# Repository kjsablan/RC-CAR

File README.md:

# RC CAR
 PCB Design for an RC CAR (Senior Project)
This is a senior design project this is currently in development and will be complete by May 2023.
The Purpose is to design a Printed Circuit Board using the Eagle software to create a circuit schematic, convert it to a board layout, generate the gerber files, and send the files out to a company to print the board. 
Then Using a microcontroller (ATMega 328P) develop firmware and create a product (RC Car)
My group has completed creating the board and now are building the RC Car.
All files (Project Report/Journal article) are still not completed and will be complete at the end of this semester (May 2023)

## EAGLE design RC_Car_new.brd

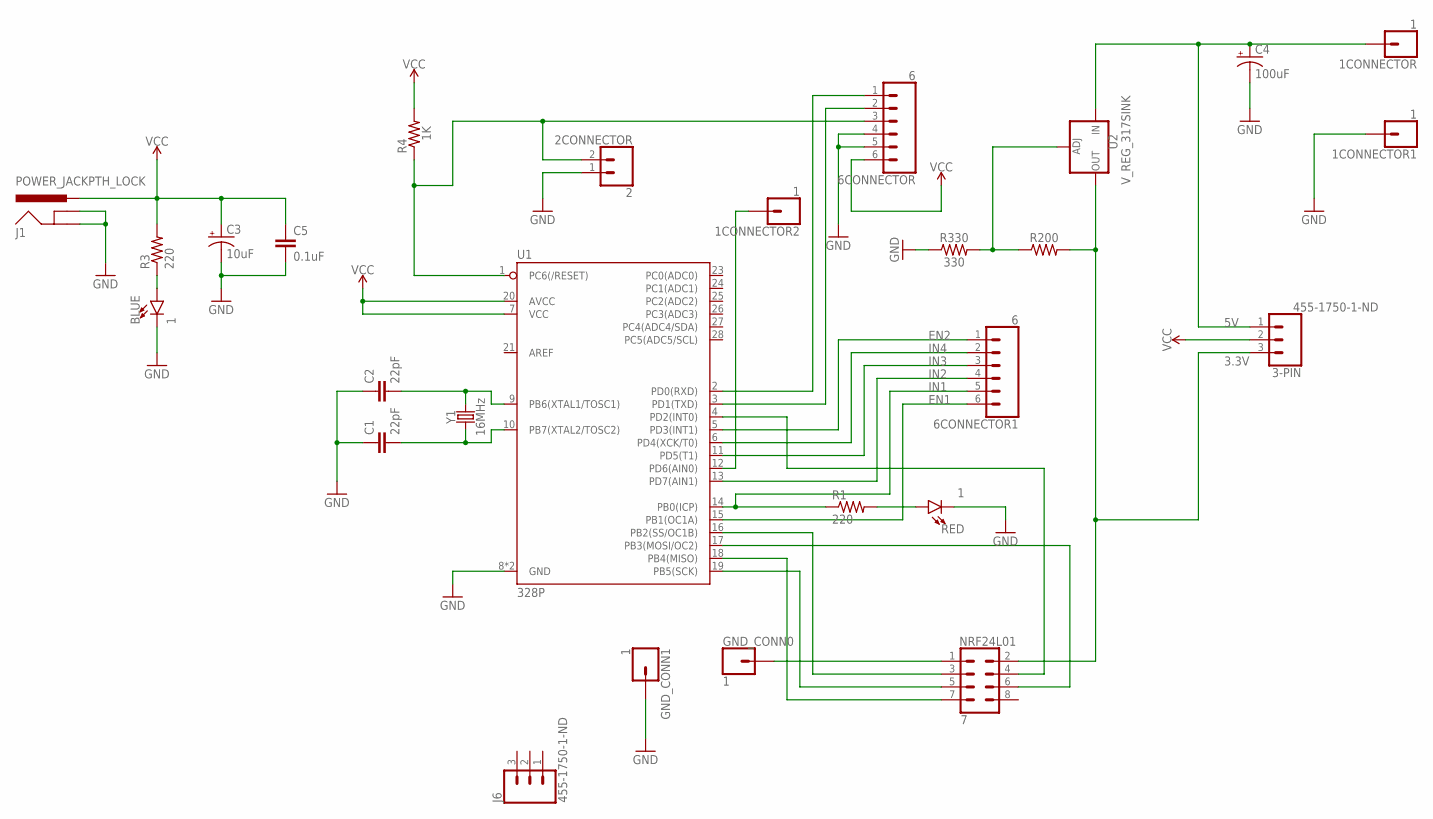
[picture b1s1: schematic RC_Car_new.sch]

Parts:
1CONNECTOR, 1CONNECTOR1, 1CONNECTOR2: 1; 1X01
2CONNECTOR: 2; 1X02
3-PIN: 455-1750-1-ND; 1X03
6CONNECTOR, 6CONNECTOR1: 6; 1X06
BLUE: 1; LED_3MM
C1, C2: 22pF; CAP-PTH-2.54
C3: 10uF; CPOL-RADIAL-2.5MM-5MM
C4: 100uF; CPOL-RADIAL-2.5MM-6.5MM
C5: 0.1uF; CAP-PTH-SMALL-KIT
GND_CONN0, GND_CONN1: 1; 1X01
J1: POWER_JACKPTH_LOCK; POWER_JACK_PTH_LOCK
J6: 455-1750-1-ND; 1X03
NRF24L01: 7; 2X4
R1, R3: 220; 0207/10
R4: 1K; 0207/10
R200: AXIAL-0.3
R330: 330; AXIAL-0.3
RED: 1; LED_3MM
U1: 328P; DIP28
U2: V_REG_317SINK; TO220-ADJ
Y1: 16MHz; HC49US

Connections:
3.3V: 3-PIN.3, NRF24L01.2, R200.P$2 (2), U2.OUT
5V: 1CONNECTOR.1, 3-PIN.1, C4.1 (+), U2.IN
EN1: 6CONNECTOR1.6, U1.15 (PB1(OC1A))
EN2: 6CONNECTOR1.1, U1.5 (PD3(INT1))
GND: 1CONNECTOR1.1, 2CONNECTOR.1, 6CONNECTOR.4, 6CONNECTOR.5, BLUE.K (C), C1.1, C2.1, C3.2 (-), C4.2 (-), C5.2, GND_CONN1.1, J1.GND, J1.GNDBREAK, R330.P$1 (1), RED.K (C), U1.8 (GND), U1.22 (GND)
IN1: 6CONNECTOR1.5, R1.1, U1.14 (PB0(ICP))
IN2: 6CONNECTOR1.4, U1.13 (PD7(AIN1))
IN3: 6CONNECTOR1.3, U1.11 (PD5(T1))
IN4: 6CONNECTOR1.2, U1.6 (PD4(XCK/T0))
unnamed: 2CONNECTOR.2, 6CONNECTOR.3, R4.1, U1.1 (PC6(/RESET))
unnamed: BLUE.A, R3.1
unnamed: C2.2, U1.9 (PB6(XTAL1/TOSC1)), Y1.2
unnamed: C1.2, U1.10 (PB7(XTAL2/TOSC2)), Y1.1
unnamed: 1CONNECTOR2.1, U1.12 (PD6(AIN0))
unnamed: R1.2, RED.A
unnamed: GND_CONN0.1, NRF24L01.1
unnamed: NRF24L01.3, U1.16 (PB2(SS/OC1B))
unnamed: 6CONNECTOR.1, U1.2 (PD0(RXD))
unnamed: 6CONNECTOR.2, U1.3 (PD1(TXD))
unnamed: R200.P$1 (1), R330.P$2 (2), U2.ADJ
unnamed: NRF24L01.4, U1.4 (PD2(INT0))
unnamed: NRF24L01.6, U1.17 (PB3(MOSI/OC2))
unnamed: NRF24L01.5, U1.19 (PB5(SCK))
unnamed: NRF24L01.7, U1.18 (PB4(MISO))
VCC: 3-PIN.2, 6CONNECTOR.6, C3.1 (+), C5.1, J1.PWR, R3.2, R4.2, U1.7 (VCC), U1.20 (AVCC)

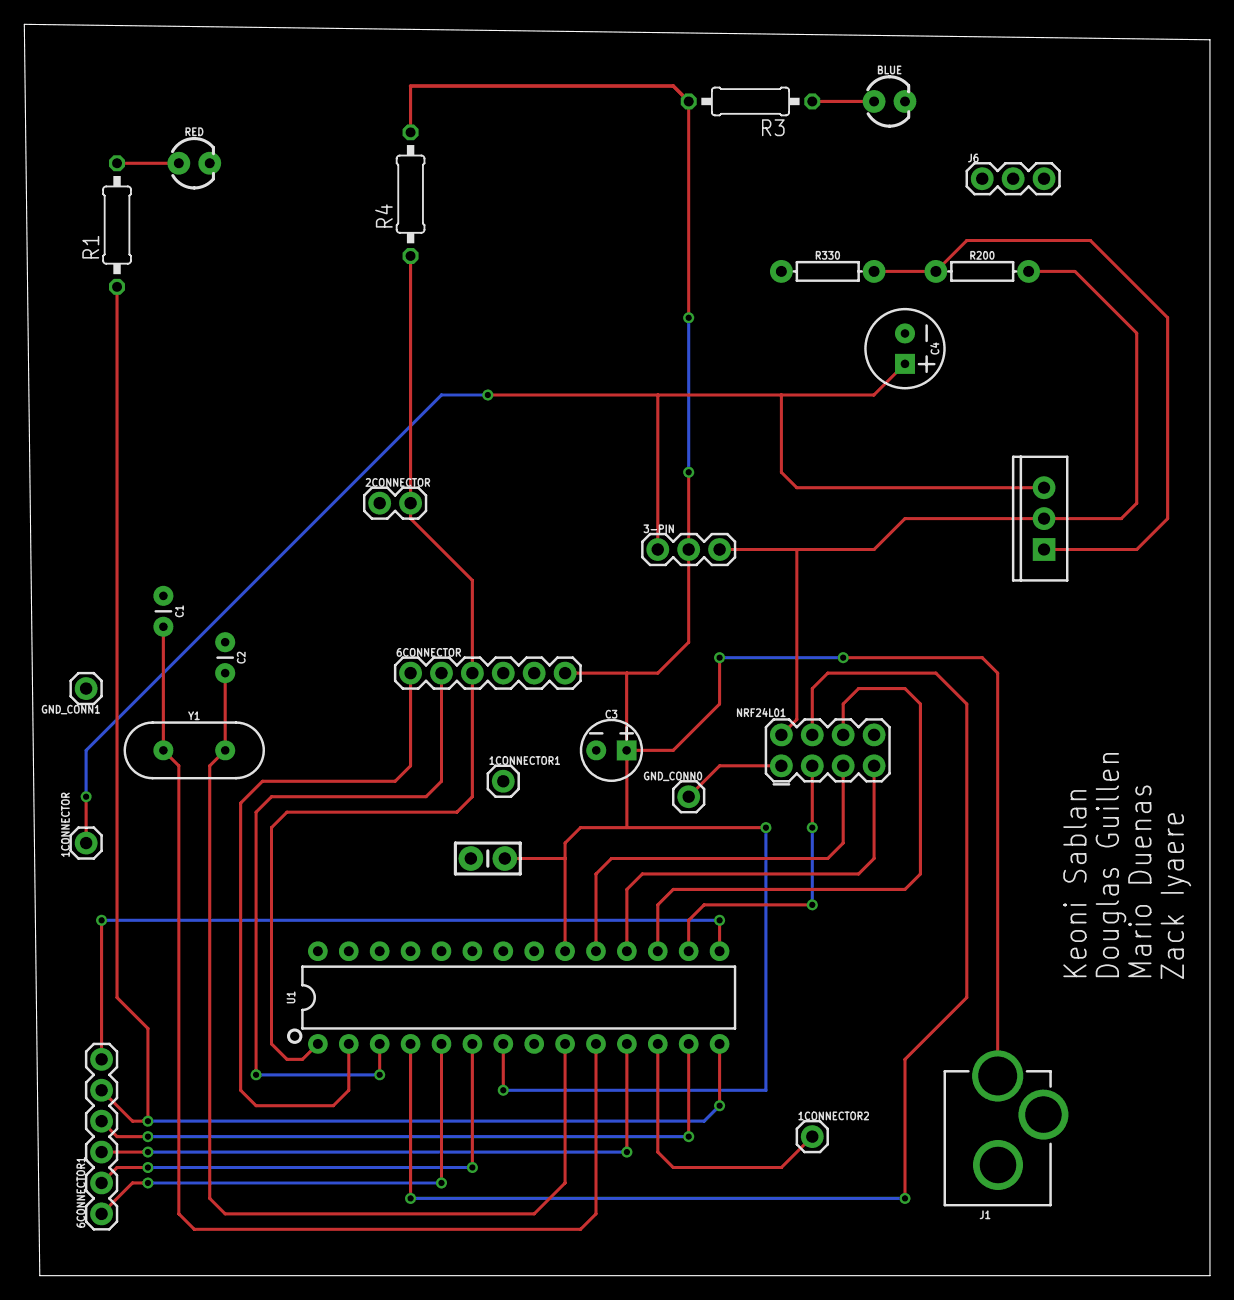
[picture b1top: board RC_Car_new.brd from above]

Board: 2 copper layers, 97.5 x 102.9 mm, 27 parts (0 on the bottom side), 25 nets.

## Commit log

2023-03-02 RC Car PCB design
    This is a senior design project this is currently in development and will be complete by May 2023

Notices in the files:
parts and their libraries:
SparkFun-Connectors: Licensing: Creative Commons ShareAlike 4.0 International - https://creativecommons.org/licenses/by-sa/4.0
